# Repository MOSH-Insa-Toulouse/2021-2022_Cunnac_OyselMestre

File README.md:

# 2021-2022_Cunnac_OyselMestre

# 1. Contexte et objectifs du projet

- [x] Réaliser une jauge de contrainte low-tech à base de graphite: [Pencil Drawn Strain Gauges and Chemiresistors on Paper](https://www.researchgate.net/publication/259846610_Pencil_Drawn_Strain_Gauges_and_Chemiresistors_on_Paper)
- [x] Concevoir un shield Arduino contenant l'amplificateur du capteur et les composants électroniques annexes (émetteur/récepteur Bluetooth, encodeur rotatif et écran OLED)
- [x] Réaliser une application mobile connectée à l'émetteur Bluetooth du capteur sous Android Studio
- [x] Évaluer le capteur sur un banc de test pour rédiger une datasheet et comparer la technologie mise en oeuvre avec un autre capteur commercial du même type

# 2. Capteur de contrainte

> Notre capteur de contrainte utilise une jauge en papier munie d'un circuit résistif en graphite. L'intérêt de l'utilisation d'une telle jauge vient de sa facilité de mise en oeuvre. La jauge est directement tracée au crayon à papier et les matériaux nécessaires (papier et crayon) sont aisément procurables à moindre coût. 

> Ce capteur low-tech exploite la théorie de la percolation au sein d’un système granulaire constitué de nanoparticules de graphite formant des feuillets. La fine couche de graphite déposée sur la feuille de papier présente un réseau percolé caractéristique. Dans ce réseau, le transport des électrons entre les nanoparticules est assuré par le mécanisme de l’effet tunnel. Ainsi, les différents chemins de percolation permettent la conduction du courant. 
Lors de l’application de déformations en tension, le réseau percolé se trouve directement étendu (le taux de percolation des réseaux diminue). Cette déformation induit une augmentation de la distance effective entre les particules de graphite au sein du réseau. Une partie des chemins de percolation sont par conséquent rompus. Ainsi, la conduction du matériau diminue, soit la résistance de la couche de graphite augmente. 
A l’inverse, lors de l’application de déformations en compression, le réseau percolé se trouve directement comprimé. Cette déformation induit une diminution de la distance effective entre les particules. Ainsi, de nouveaux chemins de percolation sont créés, la conduction du matériau augmente, soit la résistance de la couche de graphite diminue.

> Dans son principe, une jauge de contrainte est un circuit résistif dont la résistance varie avec sa déformation. En mesurant les variations de résistance de la jauge, il est possible de déduire la contrainte et la déformation appliquées. Dans ce projet, notre jauge de contrainte est alimentée par une tension régulée de 5V d'une carte Arduino UNO. La mesure du courant circulant dans la jauge constitue le signal du capteur, qui doit être amplifié et filtré.

  ## 2.1. Circuit amplificateur
 
 > La conductance des jauges en graphite que nous utilisons est très faible (de l'ordre de la dizaine de nS) et est alimentée par une tension continue de 5V. Le circuit amplificateur du capteur doit alors être en mesure d'extraire l'information d'un signal en courant de très faible intensité.
 > Dans ce projet, nous avons décidé d'utiliser un montage transimpédance constitué d'un amplificateur opérationnel (AOP) pour fournir un signal en tension suffisant au convertisseur analogique-numérique (ADC) d'une carte Arduino UNO.
 
 >   Notre jauge de contrainte est composée d'une seule résistance en série. De ce fait, notre signal est sensible aux dérives en tension de l'amplificateur. Notre AOP doit donc avoir un offset de tension en entrée très faible de manière à ce qu'il ne puisse fausser le signal fourni à l'ADC. Cela restreint notre choix d'amplificateur opérationnel. Nos jauges de contrainte en graphite ont une conductivité aux alentours de 10 nS. La jauge étant alimentée par 5V, nous nous attendons à avoir un signal en courant de l'ordre de 50 nA. En shuntant ce courant par une résistance de 100 kΩ, le signal en tension fourni à l'AOP est de 5 mV. À titre de comparaison, l'amplificateur [LM741](https://www.ti.com/lit/ds/symlink/lm741.pdf) présente un offset en entrée typique de 1 mV, et pouvant atteindre 5 mV. Ce composant n'est donc pas adapté pour notre utilisation. Ainsi notre amplificateur doit spécifiquement présenter un offset en entrée faible. Pour cette raison, nous utilisons le [LTC1050](https://www.analog.com/media/en/technical-documentation/data-sheets/1050fb.pdf), pour sa tension de dérive de 5 µV, soit 1000 fois plus faible que notre signal nominal de 5 mV.
 
 >   À partir de cet AOP, nous élaborons l'architecture du circuit amplificateur (cf. [Figure 1a](analog_circuit_images/analog_circuit.JPG)). Ce dernier dispose de trois étages de filtrage:
 >   - à l'entrée, un filtre passe-bas (R1C1) de fréquence de coupure de 16 Hz permet de filtrer les bruits en courant sur le signal d'entrée
 >   - un autre filtre passe bas de 1.6 Hz (R3C4) couplé à l'AOP permet de filtrer la composante du bruit à 50 Hz provenant du réseau électrique
 >   - à la sortie de l'amplificateur, un dernier filtre (R5C2) de 1.6 kHz permet de traiter les bruits dus à l'échantillonage de l'ADC

 >   La capacité C3 sert à filtrer les irrégularités de la tension d'alimentation de l'amplificateur. La résistance R2 sert à calibrer l'amplificateur sur le domaine de tension souhaité, qui est celui de l'ADC du micro-contrôleur. Lors de la phase de prototypage du circuit, nous avons utilisé un potentiomètre digital à la place de cette résistance pour trouver sa valeur. Enfin, la résistance R4 protège l'AOP contre les décharges électrostatiques et constitue un filtre RC avec la capacité C1 pour les bruits en tension.

**Figure 1a - Circuit amplificateur transimpédance. La résistance *Rsensor* représente la jauge de contrainte.**

**Figure 1b - Simulation AC du circuit amplificateur. Les fréquences de coupure à 1.6 Hz, 16 Hz et 1.6 kHz des trois filtres en cascade sont visibles. Cette simulation permet de vérifier le fonctionnement en fréquence de notre circuit.**

> Pour vérifier le fonctionnement normal du circuit sur LTSpice, nous simulons la déformation de la jauge par un pulse de tension en entrée (Figure 2). Ce pulse de tension génère une variation du courant en entrée de l'AOP. Virtuellement, cela représente la variation de conductance de la jauge due à sa déformation. Pour cette simulation, nous faisons varier la conductance de 5 nS à 20 nS, ce qui correspond à l'ordre de grandeur des jauges resistives utilisées. Ce faisant, nous balayons à peu près tout l'intervalle de signaux d'entrée possibles:

**Figure 2 - Simulation du fonctionnement du circuit amplificateur. Un pulse de tension permet de modéliser la déformation de la jauge et la variation du signal en courant.**

**Figure 3: Résultats de la simulation. En vert, le signal en courant fourni par la jauge et en bleu la tension de sortie de l'AOP.**

> Sur la plage de conductance prise en compte, le signal de sortie passe d'environ 240 mV à 1.05 V, ce qui ne sature pas l'ADC. L'amplitude crête-à-crête du bruit en 50 Hz est de 14 mV RMS. Ce signal est donc détectable par l'ADC qui a une sensibilité d'environ 5 mV. Le rapport signal sur bruit est de 25.6 dB pour la plus faible conductance et de 37.2 dB pour la conductance la plus élevée. Si notre signal sur cette simulation n'est fondamentalement pas considéré comme bon en terme d'instrumentation (rapport signal sur bruit inférieur à 40 dB), remarquons que naturellement, plus le signal de sortie est élevé (i.e. plus la conductance est élevée), plus le bruit à 50 Hz est écrasé par le signal. Cela signifie que plus la conductance de la jauge est élevée, plus nos mesures seront fiables et précises. Pour cette raison, nous avons tout intérêt à utiliser des jauges de contrainte de résistance relativement faibles (autour de 50 MΩ ou moins) pour nos mesures. Pour avoir une plus grande liberté sur les conductances des jauges utilisées, nous aurions pu intégrer directement sur le PCB un potentiomètre digital à la place de R2. Cela permettrait (après une étape de calibration) d'adapter le signal de sortie à la jauge résistive utilisée pour obtenir un signal optimal. Néanmoins, si nous nous restreignons à utiliser des jauges aux conductances assez élevées, alors nous obtenons un signal tout à fait acceptable.

  ## 2.2. Intégration Arduino
  > Notre capteur de contrainte est intégré avec son circuit amplificateur sur un circuit imprimé (PCB) que nous avons conçu sur le logiciel KiCad. Ce PCB est un shield pour la carte Arduino UNO qui pilote le capteur et qui intègre plusieurs composants annexes:
  > - un module de communication Bluetooth HC-05 qui permet d'envoyer les données du capteur à un smartphone doté de l'application liée au capteur
  > - un écran OLED I2C couplé à un encodeur rotatoire KY-040 qui sert d'interface utilisateur et permet de sélectionner le mode de fonctionnement du capteur (affichage de la valeur de résistance et/ou envoi des données bluetooth)

> <p align="center">
> 
> </p>

**Figure 4 - Design du PCB. Notez que la masse reliée à l'OLED et à l'encodeur est connectée à la masse de l'Arduino par un mince canal passant derrière les broches digitales 0-7 (tout en haut du PCB). Il aurait été préférable d'avoir une meilleure connexion entre les différentes zones de masse du circuit imprimé.**

  > Un défaut de fabrication du PCB a court-circuité la broche numérique 5 Arduino normalement non-connectée à la masse. Pour remédier à ce problème, nous avons dû gratter le PCB au scalpel pour déconnecter cette broche. Cependant, lors de cette opération, une partie du PCB normalement reliée à la masse est devenue flottante. La zone de masse en question alimentait l'écran OLED et l'encodeur, ce qui les rendait inutilisables. Pour rectifier cette erreur, nous avons relié cette piscine à la masse du circuit par un fil.

  > Une fois le perçage, les soudures et les rectificatifs du PCB faits, nous obtenons un shield Arduino opérationnel. Nous avons également pu effectuer nos premières mesures avec l'application mobile:

 > <div class="row" align="center">
 > 
 > 
 > </div>

**Figure 5 - En haut: shield opérationnel alimenté par une carte Arduino UNO. L'écran OLED affiche le menu déroulant navigable à l'aide de l'encodeur rotatoire. En bas: capteur en fonctionnement connecté à l'application mobile (première version).**

# 3. Programme Arduino

> Le programme Arduino permet de calculer la valeur de la résistance du capteur à partir de la valeur de tension mesurée par l'ADC de la carte. Cette mesure résistive est ensuite envoyée à l'application mobile via Bluetooth si cela est requis sur l'application. L'encodeur rotatif permet d'activer un menu sur l'OLED de choix d'affichage sur celui-ci : soit on affiche la valeur de la résistance, soit on affiche la valeur de la tension. On peut également choisir d'afficher une image ou les crédits (défilants).
> 
> A la mise en route du programme, une animation d'initialisation apparaît sur l'écran. Après cela, on a directement accès à la valeur résistive mesurée par le capteur. En tournant l'encodeur rotatoire, on peut rentrer dans le menu et sélectionner l'affichage de son choix toujours grâce à la rotation de l'encodeur. Ensuite, on valide le choix en faisant une pression sur l'encodeur.

# 4. Application mobile

  > Dans le cadre de ce projet, nous avons programmé sur Android Studio l'application mobile connectée au module Bluetooth du capteur. Cette dernière est constituée d'une seule activité sur laquelle il est possible d'acquérir les données du capteur en temps réel et de les tracer sur un graphique dynamique. Une fois les données acquises, il est possible de les exporter sous forme de texte par email ou SMS. L'application propose également d'ouvrir toute une variété d'applications pour l'export des données (réseaux sociaux et autres). Un bouton d'aide en bas de l'activité ouvre une fenêtre surgissante pour informer l'utilisateur du fonctionnement de l'application. Pour l'affichage des données sur le graphique, nous avons utilisé les bibliothèques en libre accès de la compagnie [AnyChart](https://www.anychart.com/).

 > <div class="column" align="center">
 > 
 > 
 > </div>

 **Figure 6 - À gauche: page d'accueil de la dernière version de l'application mobile. Cette capture d'écran a été prise pendant le fonctionnement du capteur. À droite: fenêtre surgissante permettant l'export des données du capteur.**

 > Pour la connection Bluetooth, le smartphone doit être appareillé au module du capteur avant de pouvoir se connecter via l'application mobile. L'application ne permet pas de choisir à quel module se connecter. En réalité, l'application est liée à un module bluetooth en particulier (celui fourni avec le capteur) et lui seul pourra être connecté au smartphone pour la transmission de données. Une piste d'amélioration consiste à afficher la liste des dispositifs appareillés pour se connecter au module souhaité. Nous n'avons cependant pas pu implémenter cette fonctionnalité par manque de temps.

 > N.B: le fichier .apk de l'application mobile est situé dans le répertoire suivant: SensorApp/app/release/. Dans ce dossier se trouve aussi  le fichier .aab (Android App Bundle), correspondant au nouveau format de publication d'applications Android ayant l'avantage d'être plus compact que le format apk (plus d'informations [ici](https://developer.android.com/guide/app-bundle)).

# 5. Mesures : Banc de test, datasheet et discussions

  ## 5.1. Banc de test
 > Pour caractériser notre capteur, nous avons utilisé notre propre banc de test réalisé par nos soins car nous n’étions pas satisfaits par ceux existants. 

 > <div class="column" align="center">
 > 
 > 
 > </div>
 
 **Figure 7 - Banc de tests mis en place.**
 
 > Ce banc de test est assez simpliste. On applique une courbure au capteur (en appuyant ou tirant sur l’extrémité de celui-ci) et on fait coulisser une pièce repère à la hauteur de cette extrémité, ce qui permet de lire la mesure de la flèche correspondante sur une règle. On peut ensuite remonter à l’angle de courbure du capteur. On réalise ainsi des mesures de résistance en fonction de l’angle de courbure aussi bien en tension qu’en compression.

  ## 5.2. Mesures et résultats
  
> Grâce à ce banc, les caractéristiques du capteur ont été déterminées par la mesure de la résistance pour différentes courbures appliquées soit différentes déformations appliquées. L’expérience a été réalisée pour plusieurs types de crayons (2H, HB et B) dont la concentration en graphite varie.
> 
> On obtient ainsi deux graphes : le premier donne la variation relative en fonction de la courbure en tension selon le type de graphite et le second de même pour la courbure en compression.

> <div class="row" align="center">
 > 
 > 
 > </div>

**Figure 8 - Caractéristique du capteur en tension (en haut) et en conpression (en bas) représentant la variation de résistance en fonction de l’angle de courbure appliqué au capteur. La pente des courbes représente la sensibilité du capteur, que l'on compare avec un autre capteur de déformation dans la section *Discussions*.**

> En tension, lors de l’augmentation de la courbure nous observons une augmentation quasi-linéaire de la résistance (et inversement). En compression, lors de l’augmentation de la courbure nous observons une diminution quasi-linéaire de la résistance (et inversement). 
> 
> En théorie, les variations de résistance sont plus importantes lorsque la dureté du crayon est plus élevée (HB > B > 2B). Sur le premier graphique, en tension, c’est bien le cas pour HB par rapport aux B et 2B cependant le 2B devrait se trouver sous le B. De la même manière, pour le deuxième graphique, en compression, le HB est bien sous le B cependant le 2B encore une fois devrait se trouver au-dessus des deux précédents, ce qui n’est pas le cas. 
Cette anomalie peut s’expliquer par plusieurs facteurs : d’abord la non-répétabilité des mesures pour ce capteur mais aussi entre autres la quantité de graphite déposée sur le papier, la pression exercée sur le papier avec le crayon et le tracé effectué par le crayon. 

## 5.3. Datasheet

> <p align="center">
> 
> </p>

**Figure 9 - Aperçu de la datasheet.**

> La datasheet regroupe l'ensemble des spécificités et caractéristiques électriques du capteur ainsi que les résultats des mesures réalisées avec le banc de test.

## 5.4. Discussions

>Ces différents résultats communiquent les avantages et les limites de ce type de jauges de contrainte.
>
> La première limite importante est la non-répétabilité de la mesure, liée entre autres à la détérioration du capteur lors des manipulations de celui-ci.
> 
> La seconde grande limite est le dépôt de graphite sur le papier. En effet ce dépôt va conditionner la mesure. Ainsi, la pression exercée par le crayon sur le papier, le nombre de passages de crayons ou encore le tracé de celui-ci vont impacter la caractérisation de la jauge.
Un procédé permettant un dépôt uniforme, précis et répétable permettrait de palier à cette limite.

 > Il est aussi intéressant de comparer notre technologie avec celle d'autres capteurs. Pour ce faire, nous avons testé avec le même banc le [Flex Sensor Spectra Symbol](https://cdn.sparkfun.com/assets/9/5/b/f/7/FLEX_SENSOR_-_SPECIAL_EDITION_DATA_SHEET_v2019__Rev_A_.pdf). Il s'agit une petite jauge résistive, de taille comparable à nos capteurs s'adaptant aussi bien à notre banc de test. Pour réaliser les mesures de résistance, étant donné que le Flex Sensor a une résistance de l'ordre de dizaines de kΩ et notre circuit conditionneur sous Arduino ne peut mesurer des résistances inférieures à 10 MΩ, nous avons utilisé un multimètre HP® 34410A pour effectuer les mesures:

> <div class="row" align="center">
 > 
 > 
 > </div>

**Figure 10 - Résultats des mesures du Flex Sensor sur le banc de test. La sensibilité correspond à la pente de la courbe qui est écrite sur les tracés. La différence d'ordre de grandeur entre la sensibilité du Flex Sensor et de nos capteurs ne nous permettent pas de représenter les mesures des deux technologies sur le même graphe.**

> La sensibilité du Flex Sensor est environ 100 fois plus faible en compression et 30 fois plus faible en tension par rapport à nos jauges de graphite (cf. Figure 8). La sensibilité élevée des jauges de contrainte en graphite représente un avantage pour la mesure de déformations - une faible déformation induit une forte variation de résistance qui est plus aisée à mesurer. Il est donc important de remarquer que notre technologie, en plus d'avoir le très fort intérêt d'être bon marché, dispose également d'avantages concrets en terme d'instrumentation et de mesure. Nous pouvons alors conclure que la confection de jauges de contrainte en graphite présente des atouts certains par rapport à d'autres capteurs du même type. De ce fait, à condition que le processus de conception du capteur soit optimisé pour garantir la répétabilité et la qualité d'une mesure, nous pouvons penser que ce genre de jauge de contraintes *low-tech* a le potentiel pour trouver sa place dans des projets d'ingénierie et d'instrumentation divers.

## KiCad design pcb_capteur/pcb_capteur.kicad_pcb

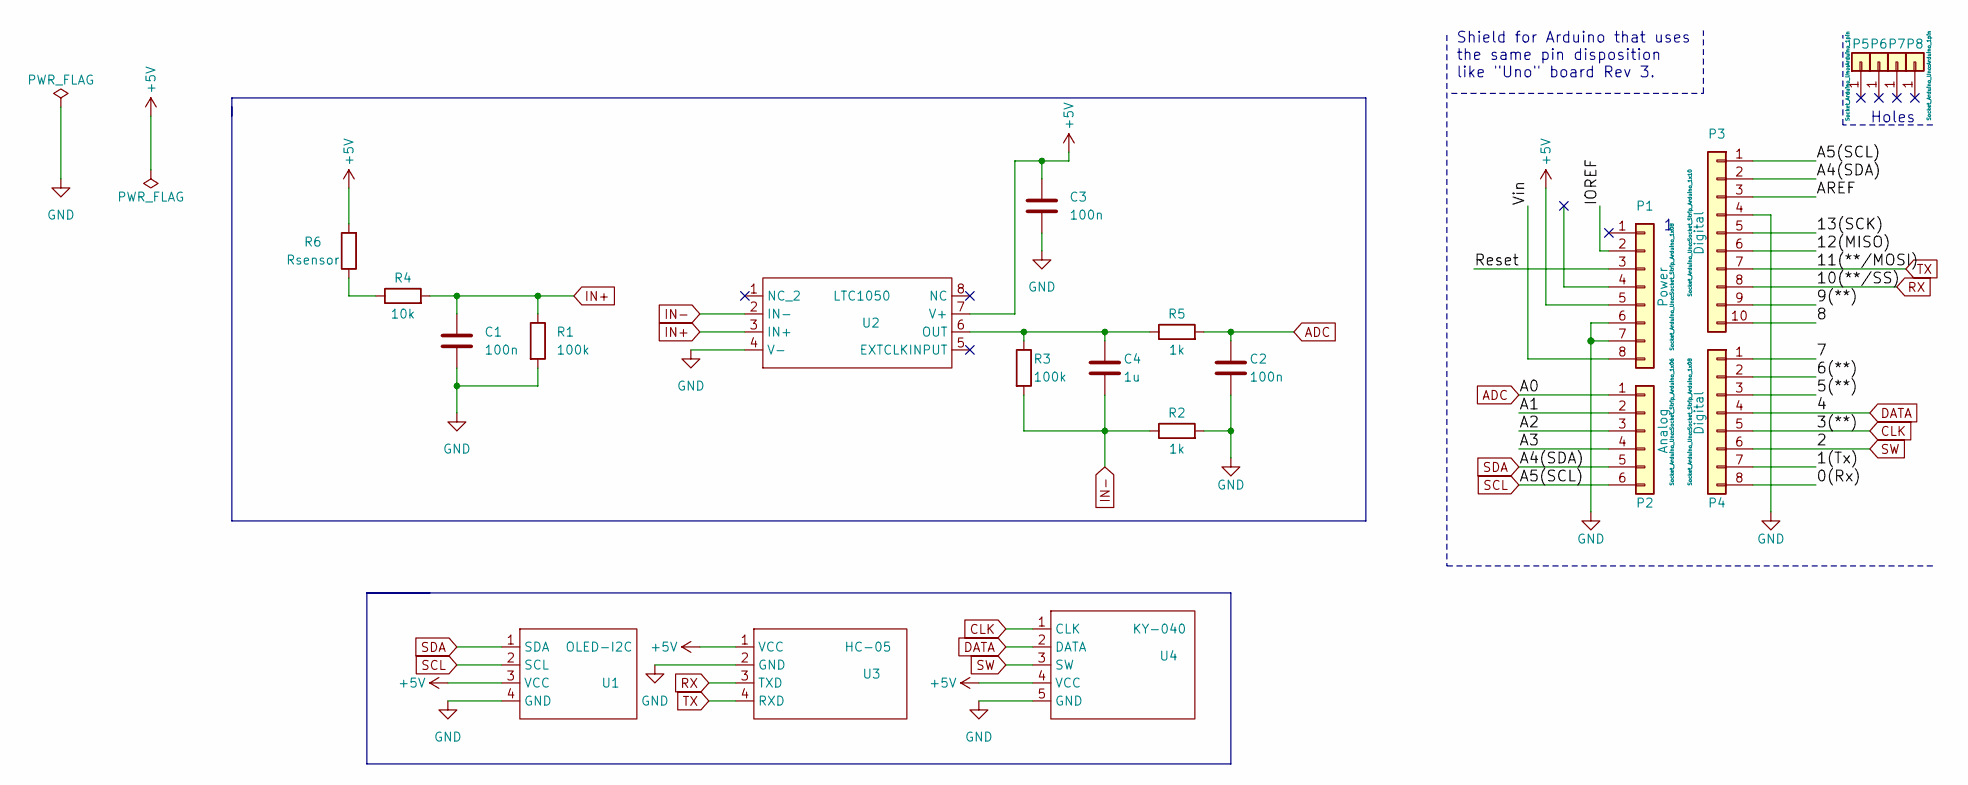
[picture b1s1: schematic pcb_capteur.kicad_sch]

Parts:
C1, C2, C3: 100n; R_Axial_DIN0204_L3.6mm_D1.6mm_P5.08mm_Horizontal
C4: 1u; C_Rect_L7.0mm_W4.5mm_P5.00mm
P1: Power; Socket_Strip_Arduino_1x08
P2: Analog; Socket_Strip_Arduino_1x06
P3: Digital; Socket_Strip_Arduino_1x10
P4: Digital; Socket_Strip_Arduino_1x08
P5, P6, P7, P8: CONN_01X01; Arduino_1pin
R1, R3: 100k; R_Axial_DIN0204_L3.6mm_D1.6mm_P7.62mm_Horizontal
R2, R5: 1k; R_Axial_DIN0204_L3.6mm_D1.6mm_P7.62mm_Horizontal
R4: 10k; R_Axial_DIN0204_L3.6mm_D1.6mm_P7.62mm_Horizontal
R6: Rsensor; SIP-2
U1: OLED-I2C; SIP-4
U2: LTC1050; DIP-8_296_ELL
U3: HC-05; SIP-4
U4: KY-040; SIP-5

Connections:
+5V: C3.1, P1.5, R6.2, U1.3 (VCC), U2.7 (V+), U3.1 (VCC), U4.4 (VCC)
/0(Rx): P4.8
/1(Tx): P4.7
/5(**): P4.3
/6(**): P4.2
/7: P4.1
/8: P3.10
/9(**): P3.9
/12(MISO): P3.6
/13(SCK): P3.5
/A1: P2.2
/A2: P2.3
/A3: P2.4
/AREF: P3.3
/IOREF: P1.2
/Reset: P1.3
/Vin: P1.8
ADC: C2.1, P2.1, R5.2
CLK: P4.5, U4.1 (CLK)
DATA: P4.4, U4.2 (DATA)
GND: C1.2, C2.2, C3.2, P1.6, P1.7, P3.4, R1.2, R2.2, U1.4 (GND), U2.4 (V-), U3.2 (GND), U4.5 (GND)
IN+: C1.1, R1.1, R4.2, U2.3 (IN+)
IN-: C4.2, R2.1, R3.2, U2.2 (IN-)
unnamed: C4.1, R3.1, R5.1, U2.6 (OUT)
unnamed: R4.1, R6.1
RX: P3.8, U3.3 (TXD)
SCL: P2.6, P3.1, U1.2 (SCL)
SDA: P2.5, P3.2, U1.1 (SDA)
SW: P4.6, U4.3 (SW)
TX: P3.7, U3.4 (RXD)

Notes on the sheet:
Holes
Shield for Arduino that uses the same pin disposition like "Uno" board Rev 3.

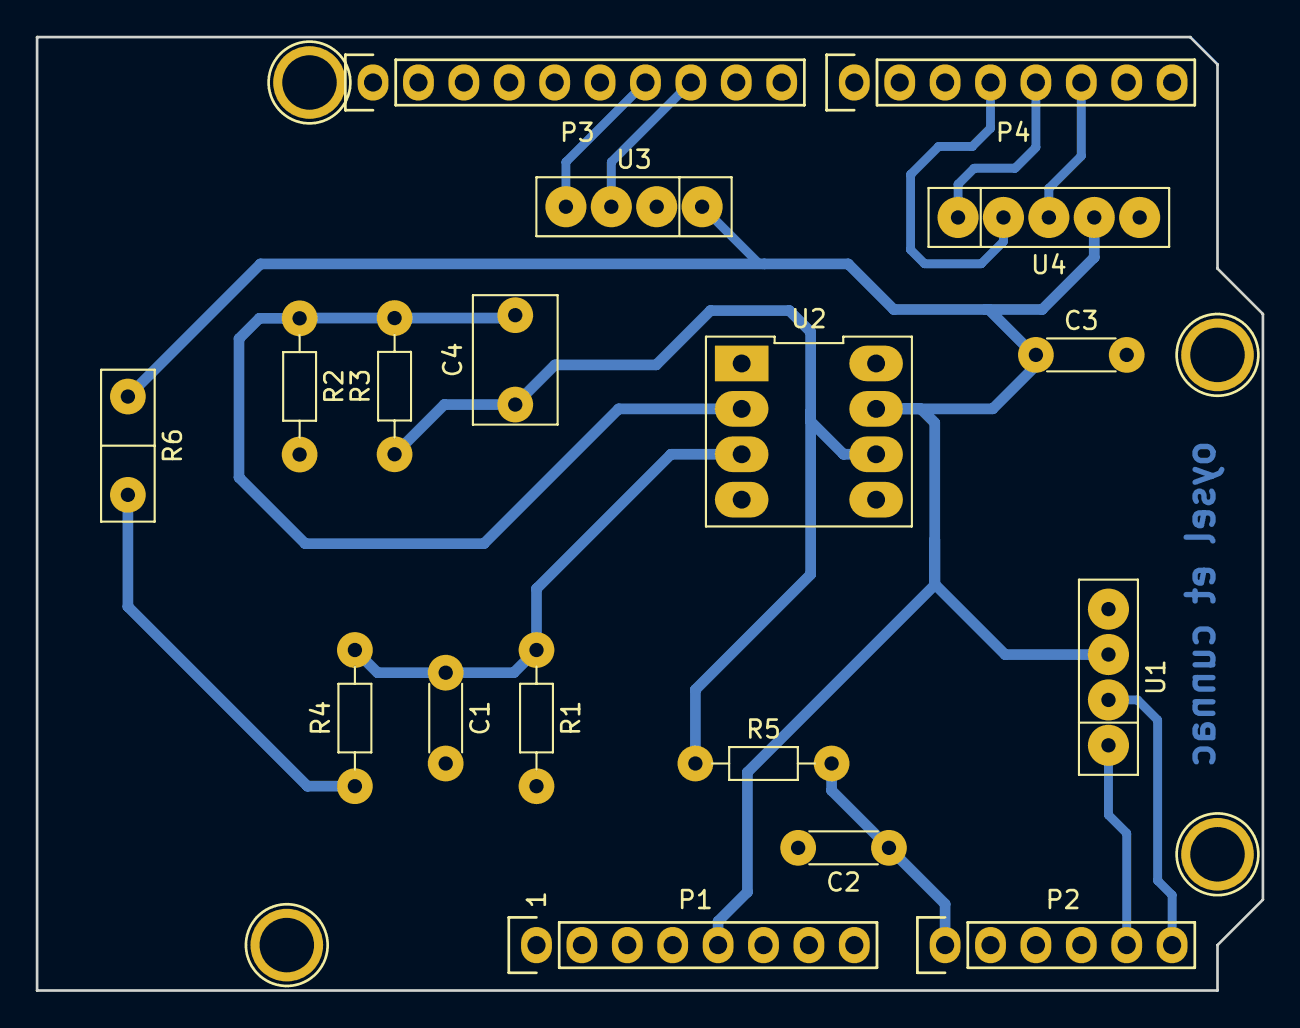
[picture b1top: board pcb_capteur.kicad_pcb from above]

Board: 2 copper layers, 68.6 x 53.3 mm, 22 parts (0 on the bottom side), 14 nets.

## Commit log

2022-03-15 Second commit
2022-03-16 Third commit
2022-03-16 Fourth commit
2022-03-22 Fifth commit
2022-03-25 Sixth commit
2022-03-31 Seventh commit
2022-04-06 First App Commit
2022-04-07 Second App Commit
2022-04-09 Third app commit
2022-04-09 Alpha App Commit
2022-04-10 analog circuit jpg
2022-04-11 Spice Simulation Images
2022-04-12 app update
2022-04-12 Global commit
2022-04-14 Latest App Commit
2022-04-14 update readme and pics
2022-04-15 arduino commit
2022-04-15 Final App Commit
2022-04-16 Update App and measurements
2022-04-16 App images
2022-04-16 App commit
2022-04-16 README update
2022-04-16 README immg html test commit
2022-04-16 README img html test commit
2022-04-16 README Arduino
2022-04-17 README and APK commit
2022-04-17 .aab extension commit
2022-04-17 APK and AAB release commit
2022-04-17 rm build files
2022-04-17 Final APK AAB commit
2022-04-17 Images Readme
2022-04-17 Ajout parties Yohan Readme
2022-04-17 Datasheet & arduino
2022-04-21 app and flex sensor commit
2022-04-22 README commit
